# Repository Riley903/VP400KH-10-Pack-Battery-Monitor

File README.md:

# Battery Back-up System

This project is the entriety of the NiCd battery back-up system used in my parents' house for emergency power in the event of a power failure.

## Original Goal

The original goal of this project was to provide power to a water pump in the event of a power failure to provide water pressure to the house.

Recycling old heavy NiCd aircraft batteries in packs of 10 cells to provide 12V would be the electrical storage since it was free and would not need to be portable.

Several of these packs, originally 4 was deemed sufficient, would be used to power a 12V water pump from the recreational boating industry which provided the necessary 50psi at a reasonable flow rate. 

In addition to this battery storage solution, we planned to designa and build a small test unit that could calculate each cell's capacity such that we could grade them and organize them in packs of similar cells. Having 100s of cells, this is a must.

## Changes to the Original Goal

We were surprised by how effective the system was working as is with 4 packs and the pump, thus we decided to introduce 4 more packs and run an inverter to the house's main panel where it could be distributed through breakers to specific areas of the house. This would be useful for powering the lights and small appliances such as LED TVs, phone chargers, computers, and possibly the fridges and freezers.

## Some Future Plans

- Adding the 4 additional packs is still in the works.
- Water level metering to the storage tank outside.
- Silent charger for the packs.
- Upgrade the packs to the ESP32 dev board as the main controller.
- Once the ESP32's are installed, could implement a locally hosted website to view the packs and cells.
- Battery pack controllable disconnects and connects. (Look into high power transistors/thyristors capable of switching 100s of Amperes).

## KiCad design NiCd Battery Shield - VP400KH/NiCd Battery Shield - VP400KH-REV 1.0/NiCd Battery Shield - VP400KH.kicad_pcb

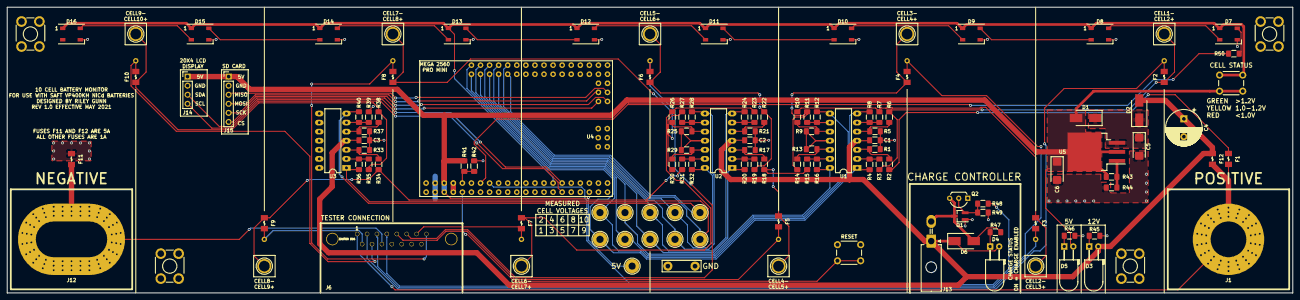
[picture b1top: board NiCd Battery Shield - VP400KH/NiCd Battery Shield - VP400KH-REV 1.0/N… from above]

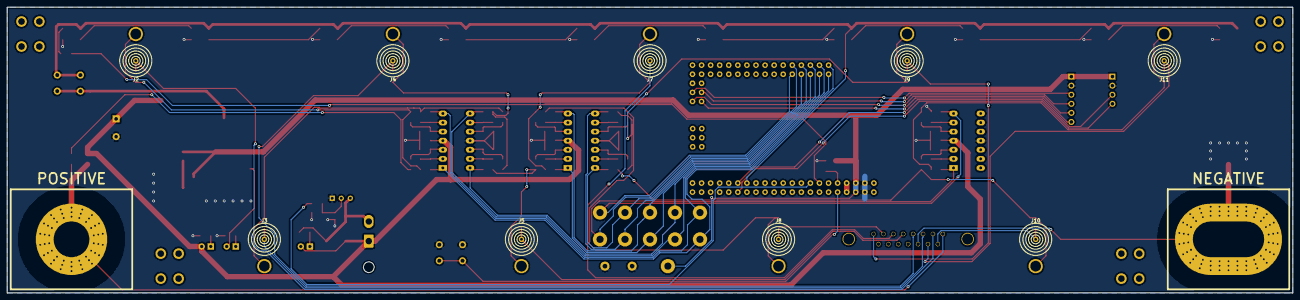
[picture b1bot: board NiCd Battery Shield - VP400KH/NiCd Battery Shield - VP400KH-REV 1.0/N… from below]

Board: 2 copper layers, 360.0 x 80.0 mm, 133 parts (9 on the bottom side), 83 nets.

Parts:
C1, C2, C3: 0.1uF; C_1206_3216Metric_Pad1.42x1.75mm_HandSolder
C4: 220uF; CP_Radial_D10.0mm_P5.00mm
C5, C6: 10uF; CP_EIA-6032-20_AVX-F_Pad2.25x2.35mm_HandSolder
D1, D2: ES3BB-13-F; D_SMB_Handsoldering
D3: 12V GREEN; LED_D5.0mm_Horizontal_O3.81mm_Z3.0mm
D4: CHARGE STATUS; LED_D5.0mm_Horizontal_O3.81mm_Z3.0mm
D5: 5V GREEN; LED_D5.0mm_Horizontal_O3.81mm_Z3.0mm
D6: 1N4007; D_SMB_Handsoldering
D7, D8, D9, D10, D11, D12, D13, D14, D15, D16: WS2812B; LED_WS2812B_PLCC4_5.0x5.0mm_P3.2mm
F1, F2, F3, F4, F5, F6, F7, F8, F9, F10: 1A; 1206_FUSE
F11, F12: 5A; 1206_FUSE
H1, H2, H3, H4: MountingHole; KEYSTONE_7795_SCREW_TERM
J1: Conn_01x01; BATTERY_POWER_CONNECTION
J2, J3, J4, J5, J7, J8, J9, J10, J11: Conn_01x01; KEYSTONE_240
J6: TESTER CONN; 15-PIN-DSUB
J12: Conn_01x01; BATTERY_POWER_CONNECTION_WIDE
J13: Conn_01x02; Molex_Mini-Fit_Jr_5569-02A2_2x01_P4.20mm_Horizontal
J14: LCD; PinHeader_1x04_P2.54mm_Vertical
J15: SD CARD; PinHeader_1x06_P2.54mm_Vertical
Q1: 4401; SOT-23_Handsoldering
Q2: 4401; TO-92L_Inline_Wide
R1, R2, R3, R4, R5, R6, R7, R8, R9, R10, R11, R12, R13, R14, R15, R16, R17, R18, R19, R20, R21, R22, R23, R24, R25, R26, R27, R28, R29, R30, R31, R32, R33, R34, R35, R36, R37, R38, R39, R40, R42: 100K; R_1206_3216Metric_Pad1.42x1.75mm_HandSolder
R41: 150K; R_1206_3216Metric_Pad1.42x1.75mm_HandSolder
R43, R44, R45, R46, R47: 620R; R_1206_3216Metric_Pad1.42x1.75mm_HandSolder
R48: 390R; R_1206_3216Metric_Pad1.42x1.75mm_HandSolder
R49: 10K; R_1206_3216Metric_Pad1.42x1.75mm_HandSolder
R50: 470R; R_1206_3216Metric_Pad1.42x1.75mm_HandSolder
SW1: RESET; SW_PUSH_6mm_H5mm
SW2: STATUS CHECK; SW_PUSH_6mm_H5mm
TP1: 1; TestPoint_THTPad_D4.0mm_Drill2.0mm
TP2: CELL 2 VOLTAGE; TestPoint_Plated_Hole_D3.0mm
TP3: 2; TestPoint_THTPad_D4.0mm_Drill2.0mm
TP4: CELL 3 VOLTAGE; TestPoint_Plated_Hole_D3.0mm
TP5: 3; TestPoint_THTPad_D4.0mm_Drill2.0mm
TP6: CELL 4 VOLTAGE; TestPoint_Plated_Hole_D3.0mm
TP7: 4; TestPoint_THTPad_D4.0mm_Drill2.0mm
TP8: CELL 5 VOLTAGE; TestPoint_Plated_Hole_D3.0mm
TP9: 5; TestPoint_THTPad_D4.0mm_Drill2.0mm
TP10: CELL 6 VOLTAGE; TestPoint_Plated_Hole_D3.0mm
TP11: 6; TestPoint_THTPad_D4.0mm_Drill2.0mm
TP12: CELL 7 VOLTAGE; TestPoint_Plated_Hole_D3.0mm
TP13: 7; TestPoint_THTPad_D4.0mm_Drill2.0mm
TP14: CELL 8 VOLTAGE; TestPoint_Plated_Hole_D3.0mm
TP15: GND; TestPoint_Bridge_Pitch7.62mm_Drill1.3mm
TP16: 8; TestPoint_THTPad_D4.0mm_Drill2.0mm
TP17: CELL 9 VOLTAGE; TestPoint_Plated_Hole_D3.0mm
TP18: 9; TestPoint_THTPad_D4.0mm_Drill2.0mm
TP19: CELL 10 VOLTAGE; TestPoint_Plated_Hole_D3.0mm
TP20: 10; TestPoint_THTPad_D4.0mm_Drill2.0mm
TP21: 5V; TestPoint_THTPad_D4.0mm_Drill2.0mm
U1, U2, U3: LM324A; DIP-14_W7.62mm_LongPads
U4: MEGA_2560_PRO_MINI-NiCd_Battery_Tester; MEGA 2560 PRO MINI_NO_MOUNTS
U5: LM1085ISX-5.0/NOPB; TO-263-3_TabPin2

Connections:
3V3: U4.7, U4.8
5V: C6.1, D1.2, D5.2, J14.1, J15.1, R41.1, R43.1, SW2.1, TP21.1, U4.5, U4.6, U5.2
12VDC_BUS: C1.1, C2.1, C3.1, C4.1, D2.2, D3.2, D4.2, D6.1, F12.2, J13.1, U1.4, U2.4, U3.4
/OP-AMPS/CELL1_FUSED: F1.2, R2.1
/OP-AMPS/CELL2_FUSED: F2.2, R3.1, R6.1, TP2.1
/OP-AMPS/CELL3_FUSED: F3.2, R7.1, R10.1, TP4.1
/OP-AMPS/CELL4_FUSED: F4.2, R11.1, R14.1, TP6.1
/OP-AMPS/CELL5_FUSED: F5.2, R15.1, R18.1, TP8.1
/OP-AMPS/CELL6_FUSED: F6.2, R19.1, R22.1, TP10.1
/OP-AMPS/CELL7_FUSED: F7.2, R23.1, R26.1, TP12.1
/OP-AMPS/CELL8_FUSED: F8.2, R27.1, R30.1, TP14.1
/OP-AMPS/CELL9_FUSED: F9.2, R31.1, R34.1, TP17.1
/OP-AMPS/CELL10_FUSED: F10.2, R35.1, R38.1, TP19.1
A0: R4.2, TP1.1, U1.1, U4.43
A1: R8.2, TP3.1, U1.7, U4.44
A2: R12.2, TP5.1, U1.8, U4.45
A3: R16.2, TP7.1, U1.14, U4.46
A4: R20.2, TP9.1, U2.1, U4.47
A5: R24.2, TP11.1, U2.7, U4.48
A6: R28.2, TP13.1, U2.8, U4.49
A7: R32.2, TP16.1, U2.14, U4.50
A8: R36.2, TP18.1, U3.1, U4.51
A9: R40.2, TP20.1, U3.7, U4.52
AREF: R41.2, R42.1, U4.9
BATTERY+: F1.1, F12.1, J1.1, J6.1
BATTERY-: F11.1, J6.11, J12.1
CHARGE_CONTROL_SIGNAL: R48.1, U4.15
CS: J15.6, U4.80
DATA: R50.1, U4.13
GND: C1.2, C2.2, C3.2, C4.2, C5.2, C6.2, D7.3, D8.3, D9.3, D10.3, D11.3, D12.3, D13.3, D14.3, D15.3, D16.3, F11.2, J14.2, J15.2, Q1.1, Q2.1, R1.2, R5.2, R9.2, R13.2, R17.2, R21.2, R25.2, R29.2, R33.2, R37.2, R39.1, R42.2, R44.2, R45.2, R46.1, R49.2, SW1.1, TP15.1, U1.11, U2.11, U3.11, U4.3, U4.4
MISO: J15.3, U4.77
MOSI: J15.4, U4.78
unnamed: C5.1, D1.1, D2.1, U5.3
unnamed: D3.1, R45.1
unnamed: D4.1, R47.1
unnamed: D5.1, R46.2
unnamed: D6.2, J13.2, Q1.3, Q2.3, R47.2
unnamed: D7.2, D8.4
unnamed: D7.4, R50.2
unnamed: D8.2, D9.4
unnamed: D10.2, D11.4
unnamed: D9.2, D10.4
unnamed: D11.2, D12.4
unnamed: D12.2, D13.4
unnamed: D13.2, D14.4
unnamed: D14.2, D15.4
unnamed: D15.2, D16.4
unnamed: F2.1, J2.1, J6.2
unnamed: F3.1, J3.1, J6.3
unnamed: F4.1, J4.1, J6.4
unnamed: F5.1, J5.1, J6.5
unnamed: F6.1, J6.6, J7.1
unnamed: F7.1, J6.7, J8.1
unnamed: F8.1, J6.8, J9.1
unnamed: F9.1, J6.9, J10.1
unnamed: F10.1, J6.10, J11.1
unnamed: Q1.2, Q2.2, R48.2, R49.1
unnamed: R1.1, R2.2, U1.3
unnamed: R3.2, R4.1, U1.2
unnamed: R5.1, R6.2, U1.5
unnamed: R7.2, R8.1, U1.6
unnamed: R9.1, R10.2, U1.10
unnamed: R11.2, R12.1, U1.9
unnamed: R13.1, R14.2, U1.12
unnamed: R15.2, R16.1, U1.13
unnamed: R17.1, R18.2, U2.3
unnamed: R19.2, R20.1, U2.2
unnamed: R21.1, R22.2, U2.5
unnamed: R23.2, R24.1, U2.6
unnamed: R25.1, R26.2, U2.10
unnamed: R27.2, R28.1, U2.9
unnamed: R29.1, R30.2, U2.12
unnamed: R31.2, R32.1, U2.13
unnamed: R33.1, R34.2, U3.3
unnamed: R35.2, R36.1, U3.2
unnamed: R37.1, R38.2, U3.5
unnamed: R39.2, R40.1, U3.6
unnamed: R43.2, R44.1, U5.1
unnamed: SW1.2, U4.10
SCK: J15.5, U4.79
SCL: J14.4, U4.32
SDA: J14.3, U4.31
STATUS_CHECK: D7.1, D8.1, D9.1, D10.1, D11.1, D12.1, D13.1, D14.1, D15.1, D16.1, SW2.2, U4.29

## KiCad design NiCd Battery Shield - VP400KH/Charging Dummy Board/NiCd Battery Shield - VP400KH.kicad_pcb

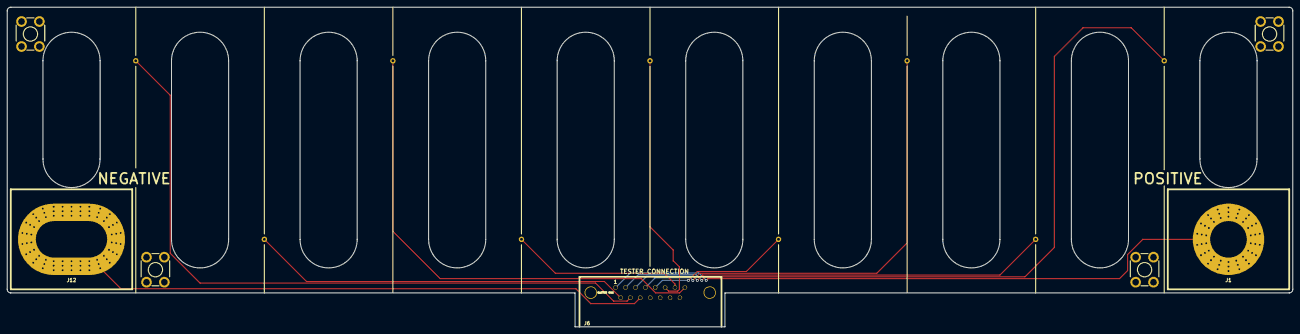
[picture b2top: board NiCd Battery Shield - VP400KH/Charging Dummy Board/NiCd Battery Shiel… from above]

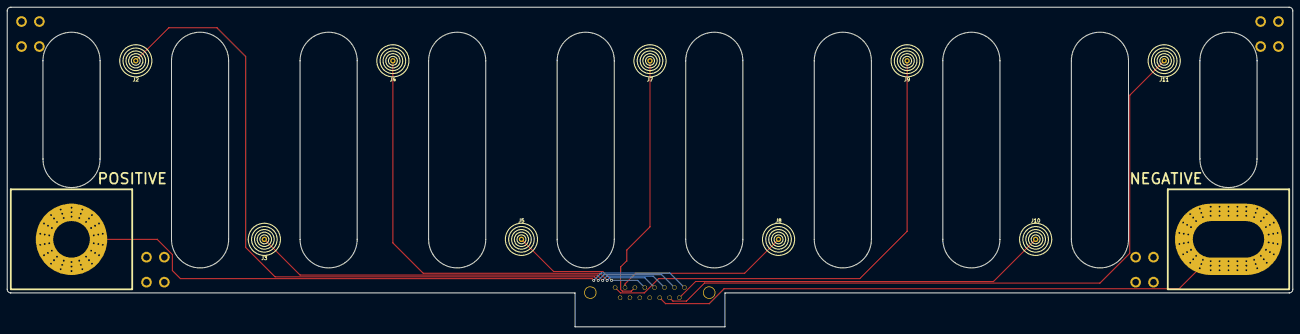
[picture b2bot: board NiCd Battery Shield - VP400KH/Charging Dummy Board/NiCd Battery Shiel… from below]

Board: 2 copper layers, 360.0 x 89.5 mm, 16 parts (9 on the bottom side), 11 nets.

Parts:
H1, H2, H3, H4: MountingHole; KEYSTONE_7795_SCREW_TERM
J1: Conn_01x01; BATTERY_POWER_CONNECTION
J2, J3, J4, J5, J7, J8, J9, J10, J11: Conn_01x01; KEYSTONE_240
J6: TESTER CONN; 15-PIN-DSUB
J12: Conn_01x01; BATTERY_POWER_CONNECTION_WIDE

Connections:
unnamed: J1.1, J6.1
unnamed: J2.1, J6.2
unnamed: J3.1, J6.3
unnamed: J4.1, J6.4
unnamed: J5.1, J6.5
unnamed: J6.6, J7.1
unnamed: J6.7, J8.1
unnamed: J6.8, J9.1
unnamed: J6.9, J10.1
unnamed: J6.10, J11.1
unnamed: J6.11, J12.1

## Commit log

2021-07-18 First Commit, initialize Repo
2021-07-20 Added KiCad Files and Test Code for Monitor
2021-07-20 Added Rev 1.1 initial commit
2021-09-28 Add files via upload
    KiCAD files
2021-09-29 Sent to manufacturer 2021-09-29
2022-11-08 Added files, need organisation
2022-11-08 Added README, modified file structure
2023-11-06 Added Code for battery testing unit
2023-11-08 Implemented ACS712-30A and ADS1115 minimum functionality
